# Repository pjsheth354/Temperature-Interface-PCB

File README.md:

# Temperature-Interface-PCB
I designed a Temperature Interface PCB using Atmega328p, LM35, 5V Regulator, 3.3 V Regulator, Op-Amp in Non Inverting State and OLED Display to display the reading on the screen.

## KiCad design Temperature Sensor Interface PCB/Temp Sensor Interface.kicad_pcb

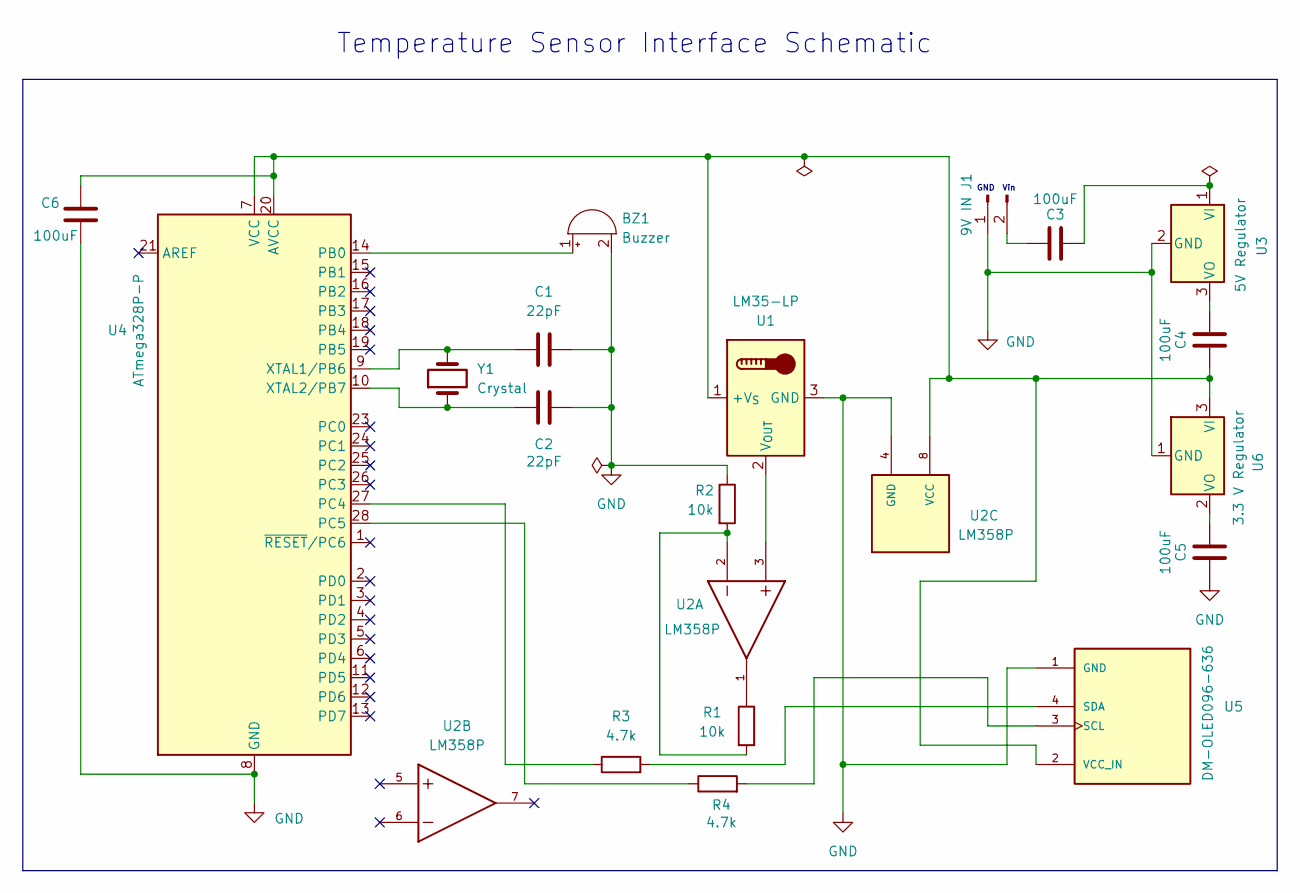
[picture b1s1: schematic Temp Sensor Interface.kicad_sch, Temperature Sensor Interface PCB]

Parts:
BZ1: Buzzer; Indicator_PUI_AI-1440-TWT-24V-2-R
C1, C2: 22pF; C_Radial_D4.0mm_H5.0mm_P1.50mm
C3, C4, C5, C6: 100uF; C_Radial_D4.0mm_H5.0mm_P1.50mm
J1: 9V IN; JST_EH_B2B-EH-A_1x02_P2.50mm_Vertical
R1, R2: 10k; R_Axial_DIN0204_L3.6mm_D1.6mm_P5.08mm_Horizontal
R3, R4: 4.7k; R_Axial_DIN0204_L3.6mm_D1.6mm_P5.08mm_Horizontal
U1: LM35-LP; TO-92_Inline
U2: LM358P; DIP794W45P254L959H508Q8; PARTREV FEBRUARY 2021
U3: 5V Regulator; TO-220-3_Vertical
U4: ATmega328P-P; DIP-28_W7.62mm
U5: DM-OLED096-636; MODULE_DM-OLED096-636; PARTREV 2018-09-10
U6: 3.3 V Regulator; TO-252-3_TabPin2
Y1: Crystal; Crystal_C26-LF_D2.1mm_L6.5mm_Vertical

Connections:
GND: BZ1.2 (-), C1.2, C2.1, C5.1, C6.1, J1.1, R2.1, U1.3 (GND), U2.4 (GND), U3.2 (GND), U4.8 (GND), U4.22 (GND), U5.1 (GND), U6.1 (GND)
unnamed: BZ1.1 (+), U4.14 (PB0)
unnamed: C3.1, J1.2
unnamed: R1.1, U2.1
unnamed: R1.2, R2.2, U2.2
unnamed: C4.1, C6.2, U1.1 (+V_{S}), U2.8 (VCC), U4.7 (VCC), U4.20 (AVCC), U5.2 (VCC_IN), U6.3 (VI)
unnamed: U1.2 (V_{OUT}), U2.3
unnamed: C3.2, U3.1 (VI)
unnamed: C4.2, U3.3 (VO)
unnamed: R3.1, U4.27 (PC4)
unnamed: R4.1, U4.28 (PC5)
unnamed: C1.1, U4.9 (XTAL1/PB6), Y1.2
unnamed: C2.2, U4.10 (XTAL2/PB7), Y1.1
unnamed: R4.2, U5.3 (SCL)
unnamed: R3.2, U5.4 (SDA)
unnamed: C5.2, U6.2 (VO)

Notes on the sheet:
Temperature Sensor Interface Schematic
Vin
GND

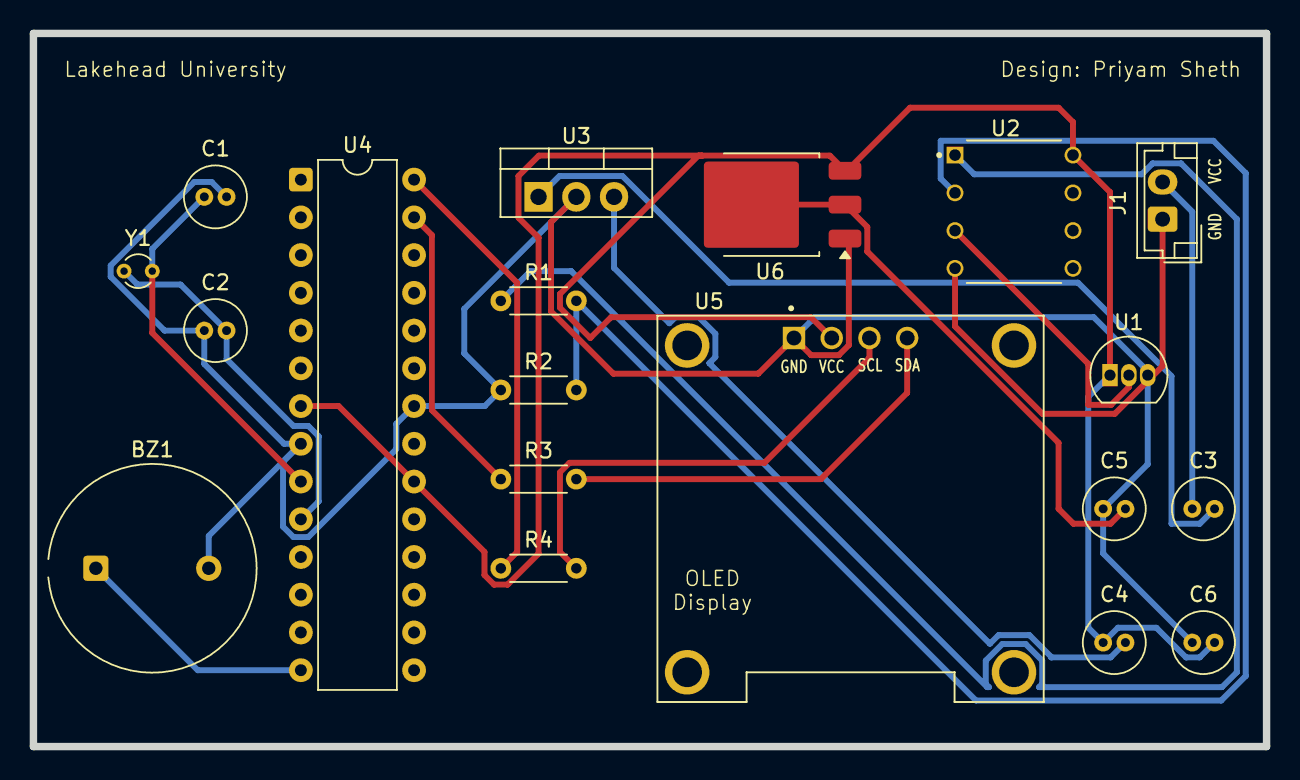
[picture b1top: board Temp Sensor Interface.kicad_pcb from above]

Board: 2 copper layers, 83.0 x 48.0 mm, 19 parts (0 on the bottom side), 16 nets.
